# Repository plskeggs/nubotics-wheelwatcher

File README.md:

# nubotics-wheelwatcher
Welcome to the open hardware and firmware repository for the Nubotics WheelWatcher encoders, 
models WW-11 (for standard size servos) and WW-12 (for specific gearhead motors).

We started designing and manufacturing the original WheelWatcher encoders in 2004.
Much has changed in the hobby robotics field in the last 12 years.  We ceased
manufacturing both products, and closed our web store after selling the last
WheelWatchers, in late 2015.

Rather than letting these designs disappear into the ether, we are opening them up so that
others may carry the torch and either build them for themselves or manufacturer
and sell them to others.  We only ask that you read, understand, and respect
the licenses we have applied.

The hardware portions are licensed under The TAPR Open Hardware License
Version 1.0 (May 25, 2007).  See the file hardware/LICENSE.TXT or find it here:
http://www.tapr.org/OHL.

The firmware portions are licensed under the Gnu Public License (GPL) v3
(June 29, 2007).  See the file code/WW-1x-firmware/COPYING or find it here:
http://www.gnu.org/licenses/.

The example programs are provided as-is, public domain.

January 2016, Noetic Design, Inc.

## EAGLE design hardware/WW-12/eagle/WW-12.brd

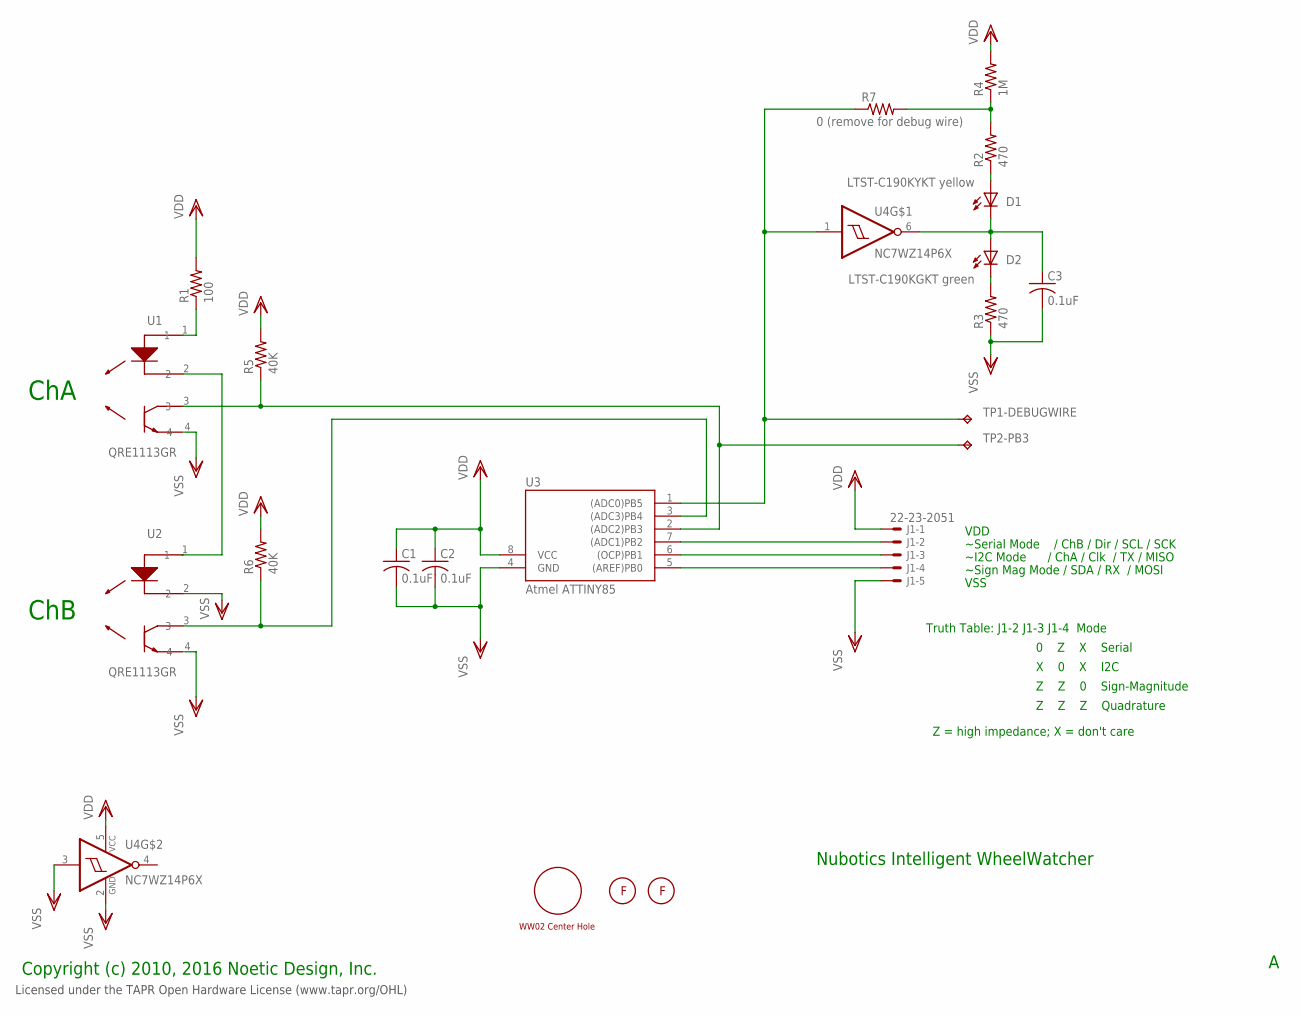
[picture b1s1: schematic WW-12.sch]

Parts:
C1, C2, C3: 0.1uF; C0603
D1: LTST-C190KYKT yellow; CHIP-LED0603
D2: LTST-C190KGKT green; CHIP-LED0603
FM1, FM2: FIDUCIAL2MMCIRCLE; FIDUCIAL_2MMCIRCLE
J1: 22-23-2051
R1: 100; R0603
R2, R3: 470; R0603
R4: 1M; R0603
R5, R6: 40K; R0603
R7: 0 (remove for debug wire); R0603
TP1-DEBUGWIRE, TP2-PB3: DEBUG WIRE; B1,27
U1, U2: QRE1113GR; 4TSOP
U3: Atmel ATTINY85; SOIC8
U4: NC7WZ14P6X; SOT65P210X110-6AN_SC88_SC70-6
U$1: WW02-CENTER

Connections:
unnamed: U1.2, U2.1
unnamed: R1.1, U1.1
unnamed: R5.1, TP2-PB3.TP, U1.3, U3.2 ((ADC2)PB3)
unnamed: R6.1, U2.3, U3.3 ((ADC3)PB4)
unnamed: D1.A, R2.1
unnamed: C3.1, D1.C, D2.A, U4.6 (O)
unnamed: D2.C, R3.2
unnamed: R2.2, R4.1, R7.2
unnamed: J1.2, U3.7 ((ADC1)PB2)
unnamed: R7.1, TP1-DEBUGWIRE.TP, U3.1 ((ADC0)PB5), U4.1 (I)
unnamed: J1.3, U3.6 ((OCP)PB1)
unnamed: J1.4, U3.5 ((AREF)PB0)
VDD: C1.1, C2.1, J1.1, R1.2, R4.2, R5.2, R6.2, U3.8 (VCC), U4.5 (VCC)
VSS: C1.2, C2.2, C3.2, J1.5, R3.1, U1.4, U2.2, U2.4, U3.4 (GND), U4.2 (GND), U4.3 (I)

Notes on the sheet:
~Serial Mode / ChB / Dir / SCL / SCK
~I2C Mode / ChA / Clk / TX / MISO
~Sign Mag Mode / SDA / RX / MOSI
VDD
VSS
Truth Table: J1-2 J1-3 J1-4 Mode
0 Z X Serial
X 0 X I2C
Z Z 0 Sign-Magnitude
Z Z Z Quadrature
Nubotics Intelligent WheelWatcher
Copyright (c) 2010, 2016 Noetic Design, Inc.
ChA
ChB
Z = high impedance; X = don't care
Licensed under the TAPR Open Hardware License (www.tapr.org/OHL)

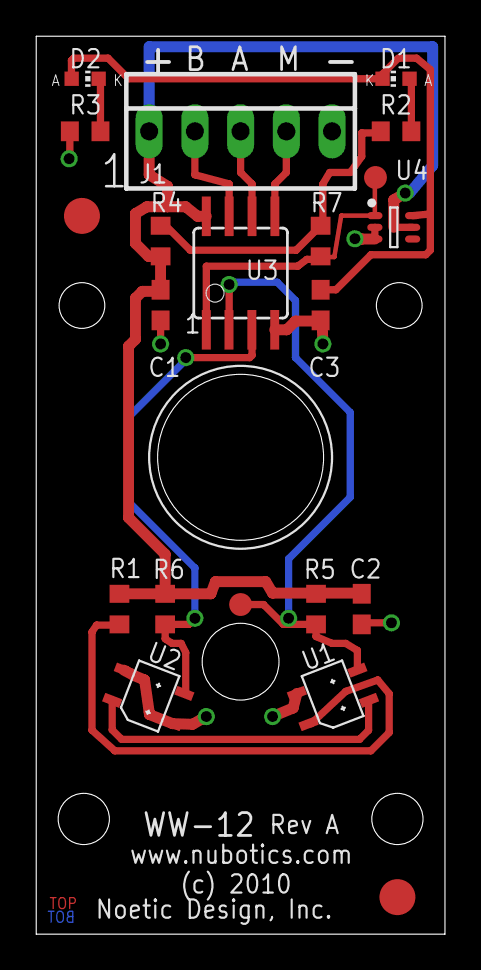
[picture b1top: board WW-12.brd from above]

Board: 2 copper layers, 22.7 x 49.9 mm, 22 parts (0 on the bottom side), 14 nets.

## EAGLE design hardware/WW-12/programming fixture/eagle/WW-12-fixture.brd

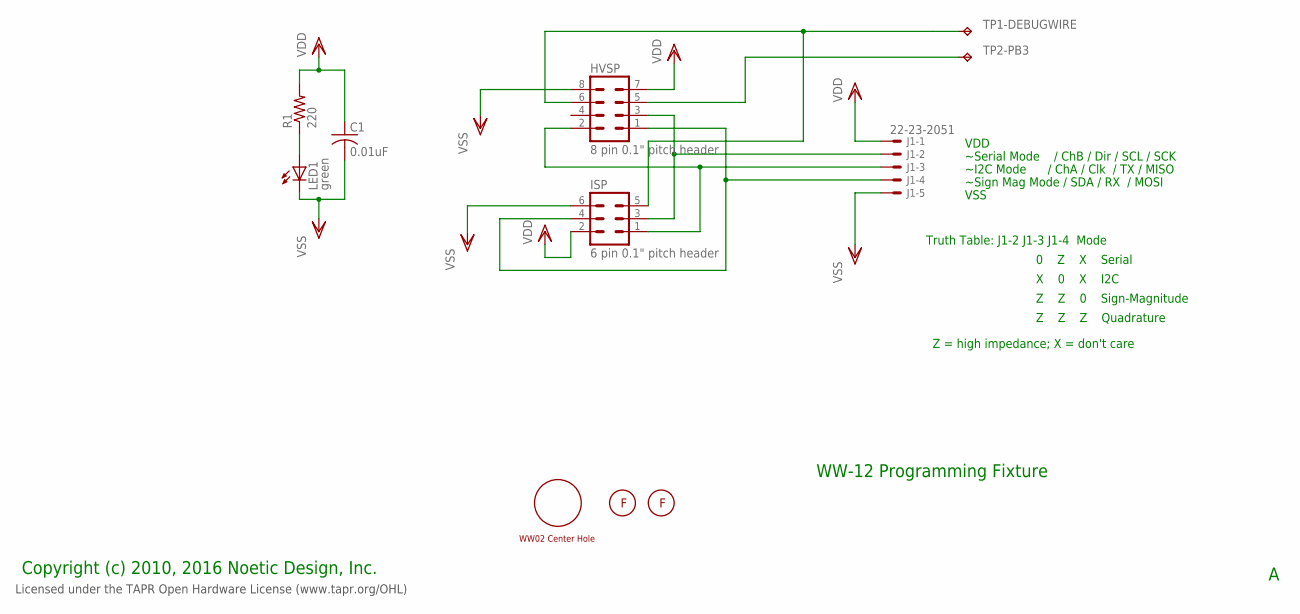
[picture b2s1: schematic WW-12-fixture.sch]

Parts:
C1: 0.01uF; C0603
FM1, FM2: FIDUCIAL2MMCIRCLE; FIDUCIAL_2MMCIRCLE
HVSP: 8 pin 0.1" pitch header; MA04-2
ISP: 6 pin 0.1" pitch header; MA03-2
J1: 22-23-2051
LED1: green; CHIP-LED0603
R1: 220; R0603
TP1-DEBUGWIRE, TP2-PB3: DEBUG WIRE; B1,27
U$1: WW02-CENTER

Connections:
unnamed: LED1.A, R1.1
PB0: HVSP.1, ISP.4, J1.4
PB1: HVSP.2, ISP.1, J1.3
PB2: HVSP.3, ISP.3, J1.2
TP1: HVSP.6, ISP.5, TP1-DEBUGWIRE.TP
TP2: HVSP.5, TP2-PB3.TP
VDD: C1.1, HVSP.7, ISP.2, J1.1, R1.2
VSS: C1.2, HVSP.8, ISP.6, J1.5, LED1.C

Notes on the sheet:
~Serial Mode / ChB / Dir / SCL / SCK
~I2C Mode / ChA / Clk / TX / MISO
~Sign Mag Mode / SDA / RX / MOSI
VDD
VSS
Truth Table: J1-2 J1-3 J1-4 Mode
0 Z X Serial
X 0 X I2C
Z Z 0 Sign-Magnitude
Z Z Z Quadrature
WW-12 Programming Fixture
Copyright (c) 2010, 2016 Noetic Design, Inc.
Z = high impedance; X = don't care
Licensed under the TAPR Open Hardware License (www.tapr.org/OHL)

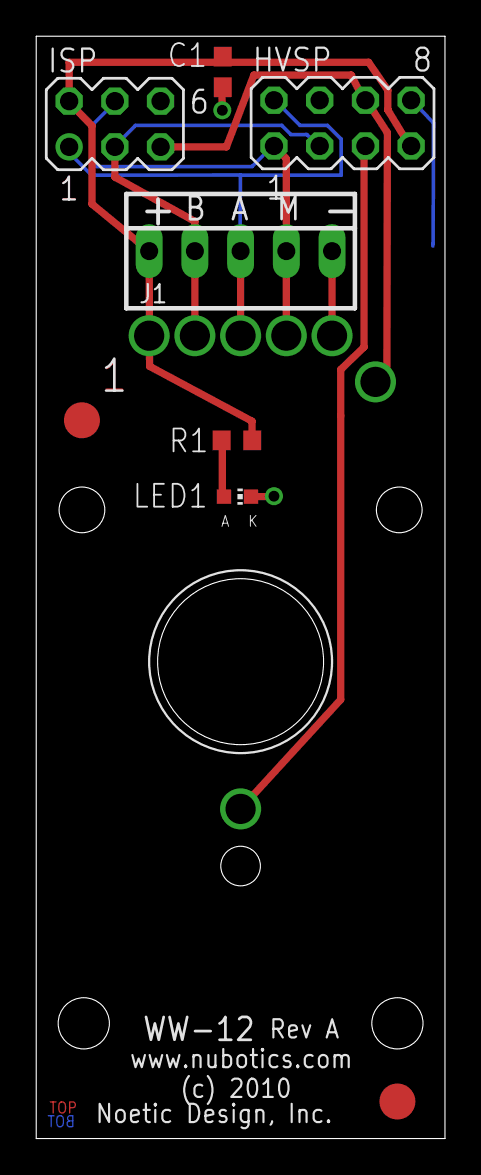
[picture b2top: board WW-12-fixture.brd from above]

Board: 2 copper layers, 22.7 x 61.2 mm, 11 parts (0 on the bottom side), 8 nets.

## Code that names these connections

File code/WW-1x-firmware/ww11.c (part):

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#define SYSCLK 8000000UL

// sign/mag pins
#define DIR_OUT PB2 // J1-2
#define CLK_OUT PB1 // J1-3

// quadrature pins
#define CHA_OUT PB1 // J1-3
#define CHB_OUT PB2 // J1-2

// serial pins
#define RX_IN  PB0  // J1-4
#define TX_OUT PB1  // J1-3

// I2C pins
#define SDA_IO PB0  // J1-4
#define SCL_IN PB2  // J1-2

// SPI pins
#define MOSI_IN  PB0 // J1-4
#define MISO_OUT PB1 // J1-3
#define SCK_IN   PB2 // J1-2

// encoder input pins
#define CHA PB3
#define CHB PB4

// cm_mode pins; if all high, quadrature mode
#define MODE_SIGN_MAG   PB0 // J1-4: if low, sign mag cm_mode
#define MODE_I2C        PB1 // J1-3: if low, I2C cm_mode
#define MODE_SERIAL     PB2 // J1-2: if low, serial cm_mode

// LED
#define LED PB5 // drive low to turn D2 (green, led_2) on; drive high to turn D1 (yellow, led_1) high

// logic
#define TRUE 1
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
    /* set up port B */
    DDRB = 0; // -- don't do this -- it turns on the LED: _BV(DDB5);
    PORTB = _BV(PB4) | _BV(PB3) | _BV(PB2) | _BV(PB1) | _BV(PB0); // turn on pull ups on inputs
    prev_b = PINB & (_BV(CHA) | _BV(CHB) | _BV(PB0));

    /* set up timer 1 */
    TCCR1 = _BV(CS11) | _BV(CS10); // clock by PCK/4, overflow at 0xff, interrupt when wrap to 0
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    _delay_ms(100); // give the user a chance to set the mode signals before sampling them
    /*
 // mode pins; if all high, quadrature mode
 #define MODE_SIGN_MAG   PB0 // J1-4: if low, sign mag mode
 #define MODE_I2C        PB1 // J1-3: if low, I2C mode
 #define MODE_SERIAL     PB2 // J1-2: if low, serial mode
    */
    switch (PINB & 0x07)
    {
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BOOTLOADER_SECTION 
SIGNAL(SIG_PIN_CHANGE)
{
    current_b = PINB & (_BV(CHA) | _BV(CHB) | _BV(PB0));
    changed_b = current_b ^ prev_b;
    prev_b = current_b;
    if ((changed_b & _BV(PB0)) && 
        !(current_b & _BV(PB0)) &&
        (cm_mode == SERIAL))
    {
        USI_UART_change_handler();
    }
    changed_b &= ~_BV(PB0); // force low, so sample_encoder() can assume the only bits ever set in changed_b are CHA and CHB
    if (changed_b & (_BV(CHA) | _BV(CHB)))
        enc_changed_time = timer_ticks;
}
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
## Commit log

2016-01-25 - first commit of WW-11 and WW-12 WheelWatcher Encoder open hardware and open source firmware repository
2016-01-25 - minor edits

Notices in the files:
code/WW-1x-firmware/ww11.c:
Copyright 2009-2012, Noetic Design, Inc.
The WW-11 firmware is free software: you can redistribute it and/or modify
it under the terms of the GNU General Public License as published by
the Free Software Foundation, either version 3 of the License, or
(at your option) any later version.
